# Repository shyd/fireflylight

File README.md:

# README #

Project based on Pimoroni's Firefly Light https://learn.pimoroni.com/tutorial/sandyj/firefly-light

Looks like this https://youtu.be/UASnjQXvQ1c

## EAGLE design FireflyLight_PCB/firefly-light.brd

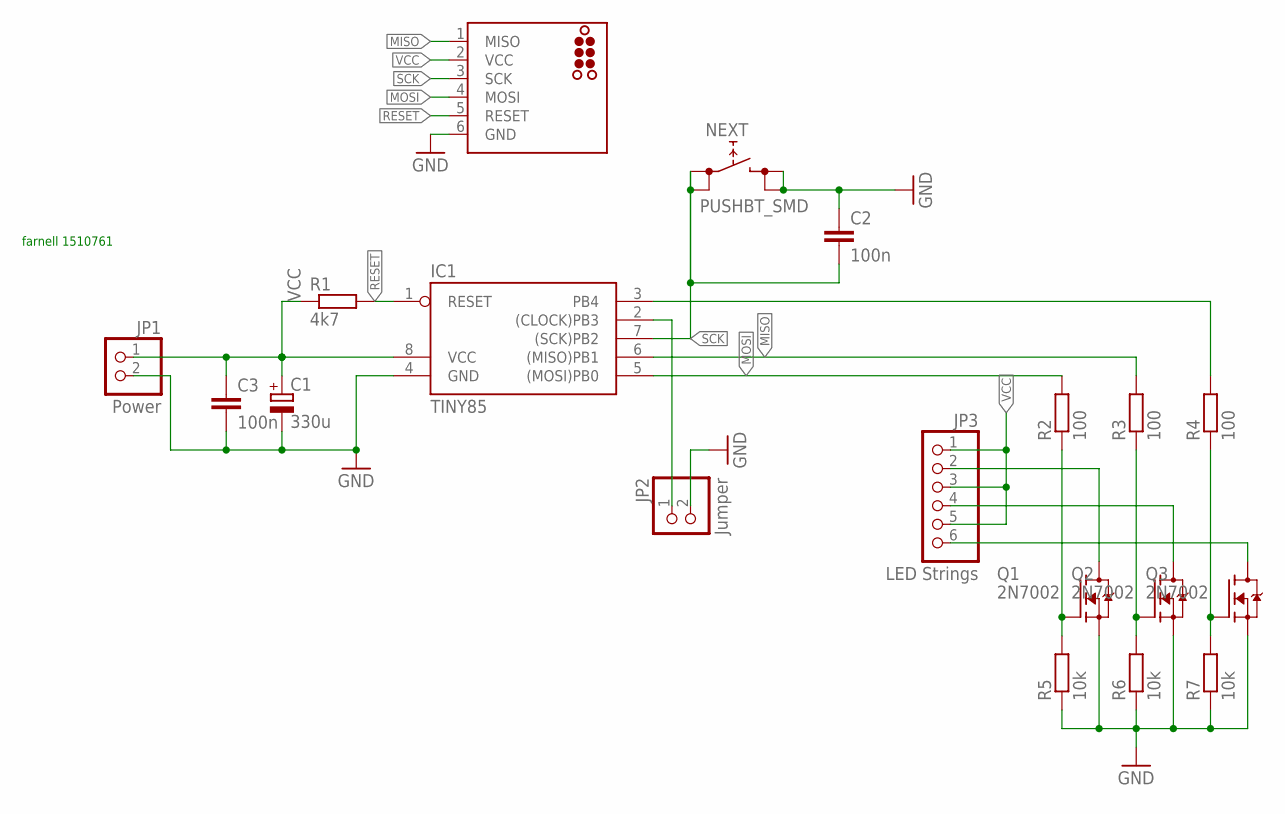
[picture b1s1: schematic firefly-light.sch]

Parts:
C1: 330u; E3,5-8
C2, C3: 100n; C0805
IC1: TINY85; SOIC8
ISP: TC2030-MCP-NL
JP1: Power; 1X02
JP2: Jumper; 1X02
JP3: LED Strings; 1X06
NEXT: PUSHBT_SMD; PUSHBUTTON
Q1, Q2, Q3: 2N7002; SOT-23
R1: 4k7; R0805
R2, R3, R4: 100; R0805
R5, R6, R7: 10k; R0805

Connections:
GND: C1.-, C2.1, C3.2, IC1.4 (GND), ISP.6 (GND), JP1.2, JP2.2, NEXT.B1 (1), NEXT.B2 (1), Q1.2 (S), Q2.2 (S), Q3.2 (S), R5.1, R6.1, R7.1
MISO: IC1.6 ((MISO)PB1), ISP.1 (MISO), R3.2
MOSI: IC1.5 ((MOSI)PB0), ISP.4 (MOSI), R2.2
unnamed: Q1.1 (G), R2.1, R5.2
unnamed: Q2.1 (G), R3.1, R6.2
unnamed: Q3.1 (G), R4.1, R7.2
unnamed: JP3.2, Q1.3 (D)
unnamed: JP3.4, Q2.3 (D)
unnamed: JP3.6, Q3.3 (D)
unnamed: IC1.3 (PB4), R4.2
unnamed: IC1.2 ((CLOCK)PB3), JP2.1
RESET: IC1.1 (RESET), ISP.5 (RESET), R1.2
SCK: C2.2, IC1.7 ((SCK)PB2), ISP.3 (SCK), NEXT.A1 (0), NEXT.A2 (0)
VCC: C1.+, C3.1, IC1.8 (VCC), ISP.2 (VCC), JP1.1, JP3.1, JP3.3, JP3.5, R1.1

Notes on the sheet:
farnell 1510761

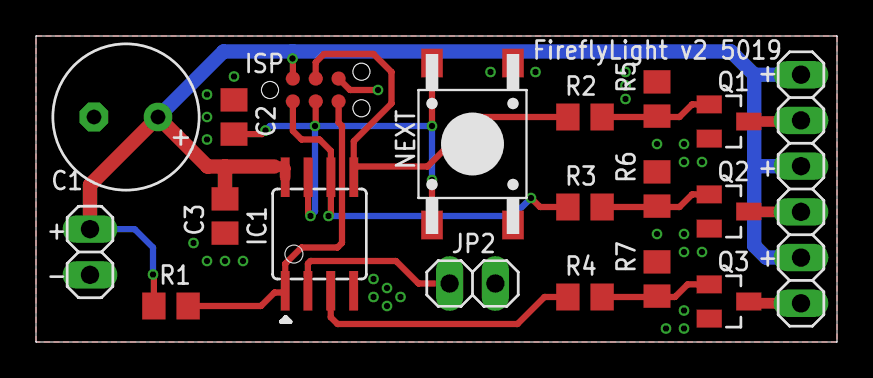
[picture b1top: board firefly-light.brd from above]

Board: 2 copper layers, 44.5 x 17.0 mm, 19 parts (0 on the bottom side), 14 nets.

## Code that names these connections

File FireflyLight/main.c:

/*
 * FireflyLight.c
 *
 * Created: 08.03.2017 12:18:04
 * Author : Dennis
 */ 

#include <avr/io.h>
#include <avr/interrupt.h>
#include <avr/pgmspace.h>
#include <avr/eeprom.h>

#define PRESCALER_MAX 32

typedef struct  
{
	volatile uint16_t position;
	volatile uint8_t prescaler;
	volatile uint8_t count;
	volatile uint8_t doSave;
} sine_t;

volatile sine_t sineA;
volatile sine_t sineB;

/* on the fly calc:
//#define PI 3.14159265f
//value = (sinf(((float)count)*PI/180.f)+1.)*254./2.;  //254 to limit pwm at top
//OCR0A = (uint8_t)lrint(value);

jsfiddle:
var count = 0;
var a=[];
for (var i=0; i<360; i++) {
	var value = (Math.sin(count*3.14159265/180)+1)*254/2;
	console.log(count, value.toFixed(0));
	a.push(parseInt(value.toFixed(0), 10));
	count = (count+1)%360;
}

var pad = function(number) {
	if (number < 10) {
		return "  " + number;
	}
	if (number < 100) {
		return " " + number;
	}
	return number;
}

var res = "";
for (var i=0; i<360; i++) {
	res += pad(a[i]) + ", ";
	if (i != 0 && (i+1) % 20 == 0) {
		res += "\n";
	}
}
console.log(res);
*/

const uint8_t sine[360] PROGMEM = {
	127, 129, 131, 134, 136, 138, 140, 142, 145, 147, 149, 151, 153, 156, 158, 160, 162, 164, 166, 168,
	170, 173, 175, 177, 179, 181, 183, 185, 187, 189, 190, 192, 194, 196, 198, 200, 202, 203, 205, 207,
	209, 210, 212, 214, 215, 217, 218, 220, 221, 223, 224, 226, 227, 228, 230, 231, 232, 234, 235, 236,
	237, 238, 239, 240, 241, 242, 243, 244, 245, 246, 246, 247, 248, 248, 249, 250, 250, 251, 251, 252,
	252, 252, 253, 253, 253, 254, 254, 254, 254, 254, 254, 254, 254, 254, 254, 254, 253, 253, 253, 252,
	252, 252, 251, 251, 250, 250, 249, 248, 248, 247, 246, 246, 245, 244, 243, 242, 241, 240, 239, 238,
	237, 236, 235, 234, 232, 231, 230, 228, 227, 226, 224, 223, 221, 220, 218, 217, 215, 214, 212, 210,
	209, 207, 205, 203, 202, 200, 198, 196, 194, 192, 191, 189, 187, 185, 183, 181, 179, 177, 175, 173,
	170, 168, 166, 164, 162, 160, 158, 156, 153, 151, 149, 147, 145, 142, 140, 138, 136, 134, 131, 129,
	127, 125, 123, 120, 118, 116, 114, 112, 109, 107, 105, 103, 101,  98,  96,  94,  92,  90,  88,  86,
	 84,  81,  79,  77,  75,  73,  71,  69,  67,  65,  64,  62,  60,  58,  56,  54,  52,  51,  49,  47,
	 45,  44,  42,  40,  39,  37,  36,  34,  33,  31,  30,  28,  27,  26,  24,  23,  22,  20,  19,  18,
	 17,  16,  15,  14,  13,  12,  11,  10,   9,   8,   8,   7,   6,   6,   5,   4,   4,   3,   3,   2,
	  2,   2,   1,   1,   1,   0,   0,   0,   0,   0,   0,   0,   0,   0,   0,   0,   1,   1,   1,   2,
	  2,   2,   3,   3,   4,   4,   5,   6,   6,   7,   8,   8,   9,  10,  11,  12,  13,  14,  15,  16,
	 17,  18,  19,  20,  22,  23,  24,  26,  27,  28,  30,  31,  33,  34,  36,  37,  39,  40,  42,  44,
  	 45,  47,  49,  51,  52,  54,  56,  58,  60,  62,  63,  65,  67,  69,  71,  73,  75,  77,  79,  81,
     84,  86,  88,  90,  92,  94,  96,  98, 101, 103, 105, 107, 109, 112, 114, 116, 118, 120, 123, 125
};

ISR(TIMER1_COMPA_vect)
{
	if (sineA.count == 0)
	{
		OCR0A = pgm_read_byte(&(sine[sineA.position]));
		OCR0B = OCR0A;
		sineA.position = (sineA.position+1)%360;
	}
	
	if (sineB.count == 0)
	{
		OCR1B = pgm_read_byte(&(sine[sineB.position]));
		sineB.position = (sineB.position+1)%360;
	}
	
	sineA.count = (sineA.count+1) % sineA.prescaler;
	sineB.count = (sineB.count+1) % sineB.prescaler;
}

ISR(INT0_vect)
{
	if (PINB & (1<<PB3))
	{
		sineA.prescaler = (sineA.prescaler+2) % PRESCALER_MAX;
		sineA.doSave = 1;
	}
	else
	{
		sineB.prescaler = (sineB.prescaler+2) % PRESCALER_MAX;
		sineB.doSave = 1;
	}
}

void sleep()
{
	ADCSRA &= ~(1<<ADEN); //disable adc
	ACSR = 0x80; // disable analouge comp
	//MCUCSR |= (1<<JTD); // disable jtag
	
	//MCUCR &= ~0x3;
	//sei();
	//MCUCR |= (1<<SM1) | (1<<SM0); // Power down
	MCUCR |= (1<<SE); // Sleep enable
	asm("sleep");
	MCUCR &= ~(1<<SE); // Sleep disable
}

int main(void)
{
	DDRB |= (1<<PB0) | (1<<PB1) | (1<<PB4);
	PORTB |= (1<<PB2) | (1<<PB3); //pullup int0, select jumper
	TCCR0A |= (1<<COM0A1);// | (1<<COM0B1);
	TCCR0A |= (1<<COM0B1) | (1<<COM0B0); //inverted B
	TCCR0A |= (1<<WGM01) | (1<<WGM00); //fast PWM
	TCCR0B |= (1<<CS00); //prescaler 0
	OCR0A = 0;
	OCR0B = 0xFF;

	TCCR1 |= (1<<CS10);// | (1<<CS12); //prescaler 0
	OCR1A = 0xFF;
	TIMSK |= (1<<OCIE1A); //int on compare match
	
	GTCCR |= (1<<PWM1B); //pwm output
	GTCCR |= (1<<COM1B1) | (1<<COM1B1); //output mode
	OCR1B = 128;
	OCR1C = 0xFF;
	
	MCUCR |= (1<<ISC01); //falling edge
	GIMSK |= (1<<INT0);
	
	//power reduction
	PRR |= (1<<PRUSI) | (1<<PRADC);
	
	sineA.count = 0;
	sineA.position = 0;
	sineA.doSave = 0;
	sineB.count = 0;
	sineB.position = 0;
	sineB.doSave = 0;
	
	sineA.prescaler = 16;
	sineB.prescaler = 10;
	
	eeprom_busy_wait();
	uint8_t val = eeprom_read_byte((uint8_t*)0x00);
	if (val >= 0x00 && val < 0xFF)
	{
		sineA.prescaler = val;
	}
	eeprom_busy_wait();
	val = eeprom_read_byte((uint8_t*)0x01);
	if (val >= 0x00 && val < 0xFF)
	{
		sineB.prescaler = val;
	}
	
	sei();
	
    /* Replace with your application code */
    while (1) 
    {
		if (sineA.doSave)
		{
			eeprom_busy_wait();
			eeprom_update_byte((uint8_t*)0x00, sineA.prescaler);
			sineA.doSave = 0;
		}
		
		if (sineB.doSave)
		{
			eeprom_busy_wait();
			eeprom_update_byte((uint8_t*)0x01, sineB.prescaler);
			sineB.doSave = 0;
		}
		sleep();
    }
}

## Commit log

2017-05-08 initial commit, added code and schematics
2017-05-08 README.md edited online with Bitbucket
2017-05-08 removed alternative schematic, edited for blog export
2017-05-08 added missing values
2019-12-09 added mosfets and ISP
2019-12-14 added pcb layout
2019-12-14 attiny is now SO8

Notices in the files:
parts and their libraries:
Meine: ©2009 ROFA.cz
